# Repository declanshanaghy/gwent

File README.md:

# Gwent Companion

<div align="center">
  
</div>

A Raspberry Pi-based digital companion for the physical card game Gwent from The Witcher III. Players use RFID-tagged physical cards; the companion tracks scores, manages game state, and guides players through the game.

```mermaid
%%{init: {
  'theme': 'base',
  'themeVariables': {
    'primaryColor': '#6d1a36',
    'primaryTextColor': '#333',
    'primaryBorderColor': '#7C4DFF',
    'lineColor': '#7C4DFF',
    'secondaryColor': '#D7CCC8',
    'tertiaryColor': '#EFEBE9',
    'fontFamily': 'Courier New',
    'fontSize': '16px'
  }
}}%%

flowchart LR
    subgraph physical["🃏 Physical Layer"]
        cards["💳 RFID Cards"]
        mat["🧵 Game Mat"]
    end

    subgraph hw["🔧 Hardware"]
        rfid["📡 RFID Reader"]
        matrix["🔢 LED Matrices"]
        touch["🖐️ 7\" Touchscreen"]
        camhw["📷 NoIR Camera"]
    end

    subgraph server["💻 Game Server"]
        gwent["🎮 gwent service"]
        mqtt_pub["📨 MQTT Publisher"]
    end

    camsvc["📷 gwent-camera\n+ nginx :80"]
    broker["📡 MQTT Broker\nMosquitto"]

    subgraph clients["👁️ Kiosk & Drivers"]
        tui["📊 gwent-tui\n(touchscreen kiosk)"]
        loop["🤖 game-loop.py"]
    end

    cards -.- rfid
    rfid --- gwent
    matrix --- gwent
    gwent --- mqtt_pub
    mqtt_pub --> broker
    broker <--> tui
    broker <--> loop
    tui --- touch
    camsvc --> camhw
    tui -.->|"/camera/*"| camsvc

    classDef hardware fill:#A1887F,stroke:#5D4037,stroke-width:2px,color:#fff,font-family:'Courier New',font-weight:bold
    classDef software fill:#BCAAA4,stroke:#5D4037,stroke-width:2px,color:#3E2723,font-family:'Courier New',font-weight:bold
    classDef data fill:#D7CCC8,stroke:#5D4037,stroke-width:2px,color:#3E2723,font-family:'Courier New',font-style:italic

    class cards,mat data
    class rfid,matrix,touch,camhw hardware
    class gwent,mqtt_pub,broker,tui,loop,camsvc software
```

## How It Works

1. The `gwent` system service runs on a Raspberry Pi, managing game state and driving all hardware. It always has a game in progress — a fresh random game is dealt at startup and after every Game Over
2. Players scan RFID-tagged cards on the reader to play cards; the 7" touchscreen runs the `gwent-tui` kiosk for assignment, menus, and live view
3. The server publishes every game state change over MQTT, including a retained full-state snapshot on `gwent/server/state`
4. Clients consume that retained snapshot — there is no HTTP API on the game server; all command and control is over MQTT (`gwent/ctrl/*` in)
5. The **gwent-tui** terminal dashboard subscribes to MQTT and renders a live view of the game on the touchscreen
6. The **game-loop.py** orchestrator pits two LLM models against each other by reading the retained snapshot and publishing moves over MQTT
7. A separate **gwent-camera** service drives a Pi NoIR camera and serves stills, an MJPEG stream, and game recordings over HTTP (nginx `/camera/*`)

## Components

### Game Server (`software/gwent/`)

The core Python service. Runs as a systemd unit (`gwent`).

- **Game stages state machine** -- DealCards, PlayRound, RoundEnd, GameOver (auto-dealt; there is no main menu)
- **MQTT command & control** -- all events and full game state are published to `gwent/` topics via a Mosquitto broker. State is a retained snapshot on `gwent/server/state`; commands (players, client-tts) come in on `gwent/ctrl/*`. No HTTP.
- **Hardware abstraction layer** -- SPI (RFID RC522), I2C (TCA9548A mux, IS31FL3731 LED matrices). The legacy SSD1306 OLED + rotary-encoder MFD drivers remain in the tree but are disabled (`GWENT_DISABLE_MFD=true`) and physically removed
- **Audio system** -- sound effects and TTS announcements (multiple providers: gTTS, ElevenLabs, OpenAI, Piper, macOS `say`)

### Terminal Dashboard (`software/gwent-tui/`)

A [Textual](https://textual.textualize.io/)-based Rich terminal app that renders a live game dashboard, running as the touchscreen kiosk (greetd → cage → kitty → gwent-tui, with a `gwent-touch` evdev bridge). Subscribes to MQTT — including the retained `gwent/server/state` snapshot — and provides hamburger-menu controls (player assignment, camera on/off, live view) plus a floating camera live-view panel. Stage-specific widgets mirror the server's state machine.

### LLM-vs-LLM Orchestrator (`.claude/skills/llm-vs/scripts/game-loop.py`)

Drives fully automated games between two LLM models. Supports multiple providers (Anthropic, OpenAI, Google Gemini, Ollama) with model aliases. Reads game state from the retained `gwent/server/state` MQTT snapshot, constructs prompts with full board context, and submits moves via MQTT.

### Camera Service (`scripts/camera-server.py`)

A standalone `gwent-camera` systemd service (system Python + picamera2) owns the Pi NoIR camera and exposes stills, an MJPEG stream, and game recordings via nginx on port 80 (`/camera/{still,stream,recordings/}`). It is also an MQTT client (`gwent/camera/ctrl` in, retained `gwent/camera/state` out) and records each game to H.264 with a 10 GiB disk budget.

### Shared Utilities (`software/gwent-shared/`)

TTS provider abstractions shared between server and TUI. No hardware dependencies.

## Hardware

| Bus | Device | Purpose |
|-----|--------|---------|
| SPI CE0 | MFRC522 | RFID card reader |
| I2C (via TCA9548A mux) | IS31FL3731 Ch 0 | Gem display (lives) |
| I2C (via TCA9548A mux) | IS31FL3731 Ch 1 | Player 1 score |
| I2C (via TCA9548A mux) | IS31FL3731 Ch 2 | Player 2 score |
| DSI / USB | 7" Touchscreen | Kiosk UI (gwent-tui) + speakers |
| CSI | Pi NoIR Camera (IMX219) | Table view, stills/stream, game recordings |

## Card Data

Each card is a JSON file in `software/data/cards/{Faction}/CardName.json`:

```json
{
  "faction": "Monsters",
  "name": "Arachas: 1",
  "strength": 4,
  "ranges": ["close"],
  "abilities": ["muster"],
  "starter": true,
  "rfid": 622264733154
}
```

Five factions: **Monsters**, **Nilfgaardian**, **Northern Realms**, **Scoiatael**, **Skellige**, plus **Neutral** cards.

## Development

```bash
# Start the dev server
bash scripts/dev-server.sh gwent start

# Dump current game state (retained snapshot)
mosquitto_sub -h localhost -u geralt -P gwent -t gwent/server/state -C 1

# Run the TUI
gwent-tui

# Run an LLM vs LLM game
python3 .claude/skills/llm-vs/scripts/game-loop.py \
  --model-p1 anthropic/sonnet --model-p2 gemini/flash
```

Always use `SIGTERM` for graceful shutdown (never `SIGKILL`) -- hardware cleanup is required.

## Documentation

| Document | Description |
|----------|-------------|
| [Architecture](design/GwentArchitecture.md) | Full system architecture reference |
| [Game Rules](design/GwentRules.md) | Canonical Gwent rules as implemented |
| [Game Stages](design/GwentGameStages.md) | State machine and flow diagrams |
| [PubSub Architecture](design/GwentPubSub.md) | MQTT messaging system design |
| [Product Requirements](design/000-product-requirements.md) | Original PRD |
| [Mermaid Style Guide](design/MermaidStyleGuide.md) | Diagram styling conventions |

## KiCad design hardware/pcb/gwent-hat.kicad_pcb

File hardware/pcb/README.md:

# Gwent HAT — KiCad project

A Raspberry Pi 4 HAT carrier PCB for the Gwent Companion. Hosts headers and Qwiic connectors so the existing breakout modules (MFRC522, SSD1306 OLED, TCA9548A mux, three IS31FL3731 charlieplex matrices, PEC11 rotary encoder) plug in without re-soldering. Targets fabrication at JLCPCB.

> Canonical hardware spec: [`design/tasks/011-hardware-specification.md`](../../design/tasks/011-hardware-specification.md). If anything in the schematic conflicts with that doc, the doc wins — fix the schematic.

## Quick facts

| | |
|---|---|
| Form factor | Raspberry Pi HAT (65 × 56.5 mm) |
| Layers | 2 |
| Substrate | FR4, 1.6 mm, 1 oz copper, ENIG (or HASL for cheap) |
| Connectors | 2×20 GPIO stacking header, 1×8 RC522 header, 1×16 OLED header, 4× Qwiic JST-SH (mux + 3 matrices), PEC11 footprint |
| Library deps | KiCad 9 built-in libraries only (Connector, Connector_Generic, Connector_JST, Switch). SparkFun KiCad library optional for prettier Qwiic 3D models. |
| Power | 5V / 3.3V tapped from Pi GPIO header (no on-board regulator) |
| Target fab | JLCPCB, 5 boards (~$5 unassembled, ~$25 with header assembly) |

## Required tools

- **KiCad 9.x** — https://www.kicad.org/download/
- **git** with submodule support
- (optional) **JLCPCB plugin for KiCad** — https://github.com/Bouni/kicad-jlcpcb-tools — generates BOM and pick-and-place files in the format JLCPCB wants

Once KiCad is installed, open `gwent-hat.kicad_pro` and KiCad will pull in the project's symbol/footprint library tables (in `sym-lib-table` / `fp-lib-table`) which point at the vendored libs in `libs/`.

## First-time setup

```bash
cd hardware/pcb
open gwent-hat.kicad_pro          # macOS
# or
xdg-open gwent-hat.kicad_pro      # Linux
```

KiCad will create the schematic (`gwent-hat.kicad_sch`) and PCB (`gwent-hat.kicad_pcb`) on first save if they don't already exist. All symbols and footprints come from KiCad's bundled libraries — no extra setup required.

### Optional: SparkFun KiCad library (for nicer Qwiic visuals)

```bash
# From hardware/pcb/
git clone --depth 1 https://github.com/sparkfun/SparkFun-KiCad-Libraries.git libs/sparkfun-kicad
# Then in KiCad: Preferences → Manage Symbol Libraries → add libs/sparkfun-kicad
#                Preferences → Manage Footprint Libraries → add libs/sparkfun-kicad/footprints
```

This isn't required — KiCad's `Connector_JST:JST_SH_*` symbols are functionally equivalent — but the SparkFun version comes with proper Qwiic-branded silkscreen and 3D models.

## How the project is organized

| File | What it is |
|---|---|
| `gwent-hat.kicad_pro` | KiCad project metadata |
| `gwent-hat.kicad_sch` | Schematic |
| `gwent-hat.kicad_pcb` | PCB layout (board outline pre-drawn to Pi HAT spec) |
| `sym-lib-table` | Project-scoped symbol library list |
| `fp-lib-table` | Project-scoped footprint library list |
| `BUILD.md` | Step-by-step schematic placement guide |
| `BOM.md` | Bill of materials with manufacturer part numbers and JLCPCB/LCSC sourcing |
| `libs/` | (Optional) Vendored EDA libraries — only needed for SparkFun Qwiic visuals |
| `fab/` | Fabrication outputs (Gerbers, drill, BOM, CPL) — only versioned zips are committed |
| `docs/netlist.md` | Canonical net-by-net pin assignments — the source of truth for the schematic |

## Workflow

1. **Schematic** — open `gwent-hat.kicad_sch` and follow [`BUILD.md`](BUILD.md) step by step. Place every symbol from the BOM, wire nets per [`docs/netlist.md`](docs/netlist.md), assign footprints, run ERC.
2. **PCB layout** — Tools → Update PCB from Schematic. Footprints will appear inside the pre-drawn board outline. Place, route, run DRC. Match design rules to JLCPCB's "2-layer, 6/6 mil min trace, 0.3 mm min hole" capability tier.
3. **Fab outputs** — File → Plot → Gerbers (use the JLCPCB-friendly settings documented in `BUILD.md`), then File → Fabrication Outputs → Drill Files. Run the JLCPCB plugin to generate BOM + CPL CSVs.
4. **Order** — zip the Gerber/drill/BOM/CPL set into `fab/gwent-hat-v1.0-jlcpcb.zip`, upload to https://jlcpcb.com, pick stackup + finish + quantity, pay.

## Versioning

- `v1.0` — initial Pi HAT carrier with breakouts on headers/Qwiic
- `v1.1` — corrections from first fab run (TBD)
- `v2.0` — integrate IS31FL3731 + LEDs and TCA9548A onto the board (TBD)

Each fab order zip is committed under `fab/gwent-hat-vN.M-jlcpcb.zip` so the as-fabbed artifact is always reproducible.

## Status

- [x] Project scaffold (this commit)
- [x] Canonical netlist documented (`docs/netlist.md`)
- [x] Bill of materials (`BOM.md`)
- [x] Build guide (`BUILD.md`)
- [x] Project file (`gwent-hat.kicad_pro`)
- [x] Schematic with all symbols placed (`gwent-hat.kicad_sch`, generated by `scripts/gen_schematic.py`)
- [ ] Schematic wired (add wires + net labels per `BUILD.md`)
- [ ] ERC clean
- [ ] Board outline drawn to Pi HAT spec on `Edge.Cuts` layer
- [ ] PCB placement
- [ ] PCB routing
- [ ] DRC clean
- [ ] Gerbers exported
- [ ] BOM + CPL generated
- [ ] First boards ordered

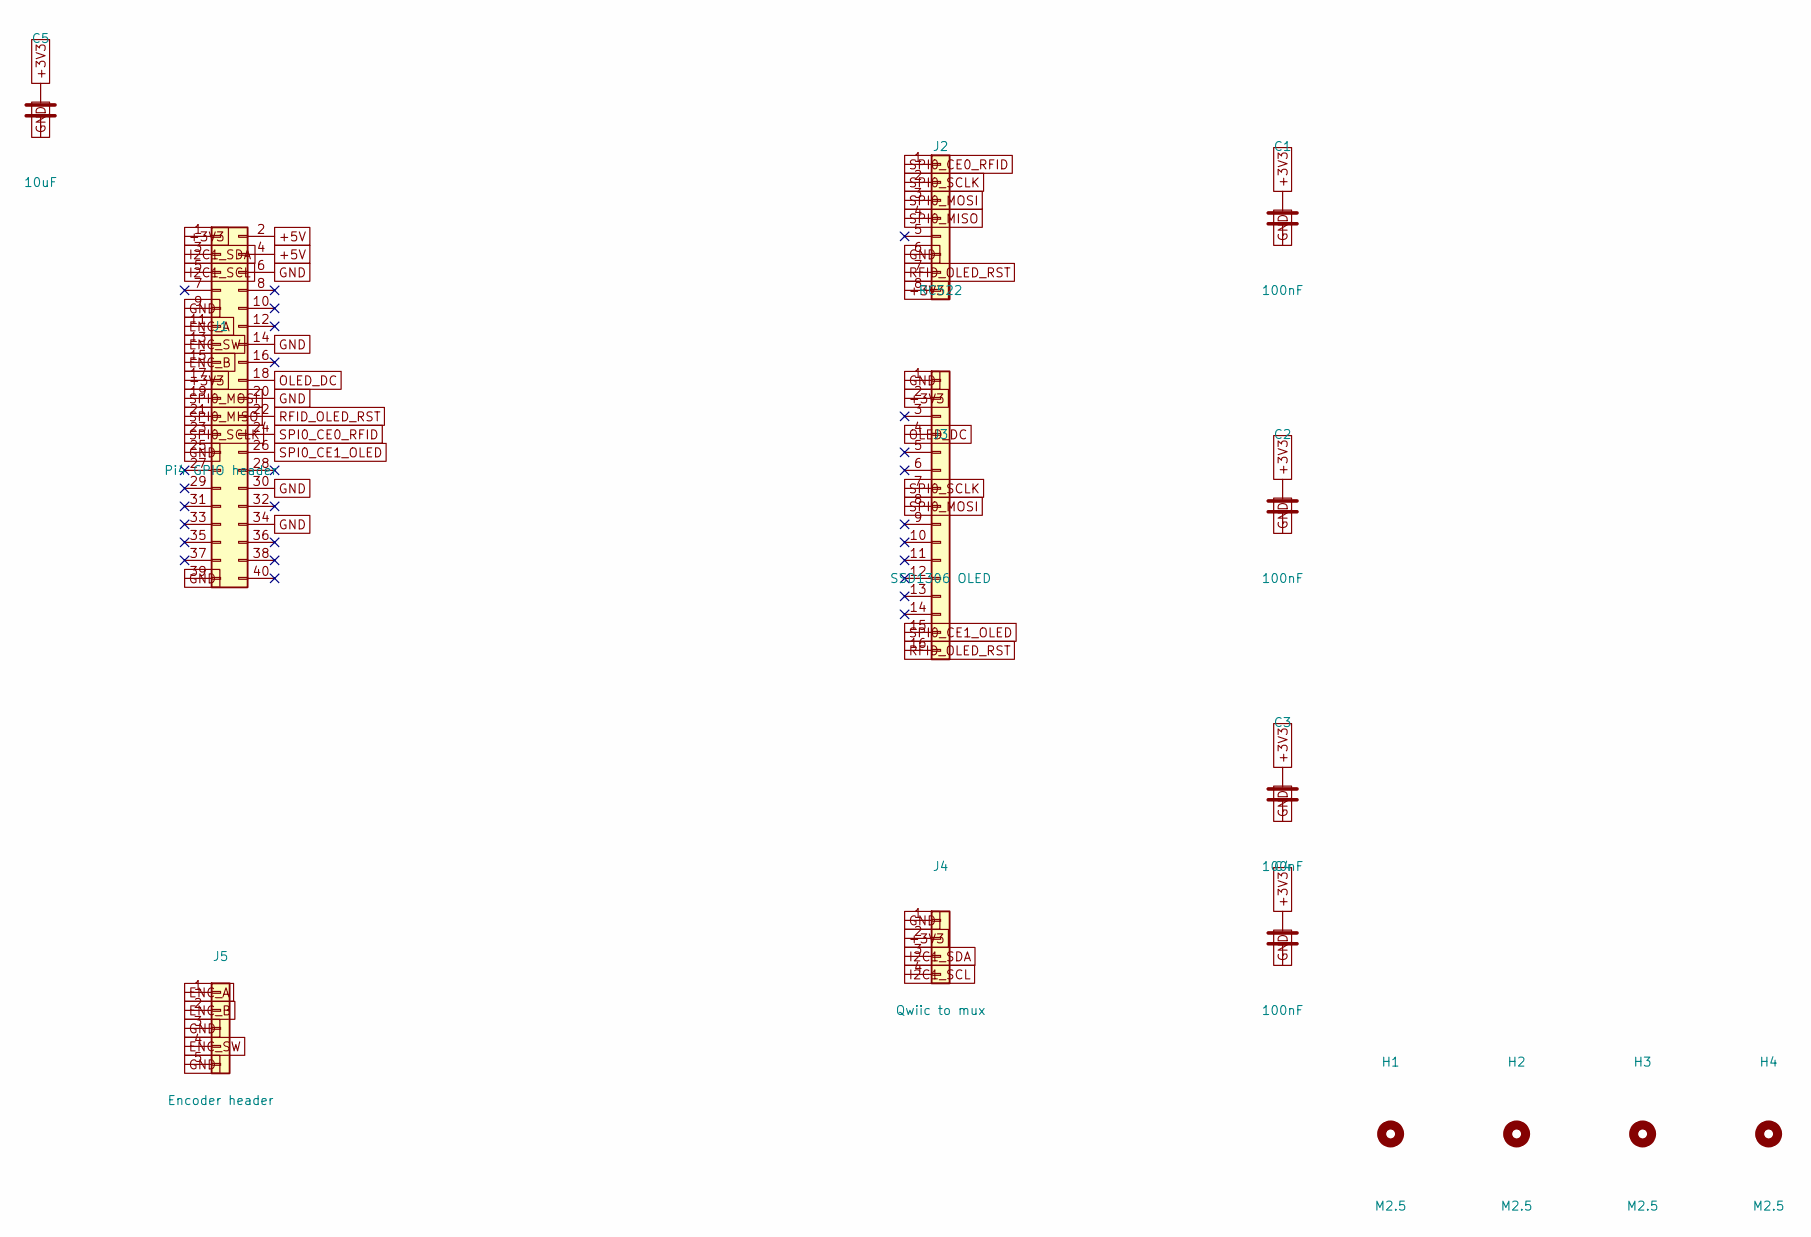
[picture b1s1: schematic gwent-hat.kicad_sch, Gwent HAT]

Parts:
C1, C2, C3, C4: 100nF; C_0805_2012Metric
C5: 10uF; C_0805_2012Metric
H1, H2, H3, H4: M2.5; MountingHole_2.7mm_M2.5_DIN965_Pad
J1: Pi4 GPIO header; PinHeader_2x20_P2.54mm_Vertical
J2: RC522; PinHeader_1x08_P2.54mm_Vertical
J3: SSD1306 OLED; PinHeader_1x16_P2.54mm_Vertical
J4: Qwiic to mux; JST_SH_SM04B-SRSS-TB_1x04-1MP_P1.00mm_Horizontal
J5: Encoder header; PinHeader_1x05_P2.54mm_Vertical

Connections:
+3V3: C1.1, C2.1, C3.1, C4.1, C5.1, J1.1, J1.17, J2.8, J3.2, J4.2
+5V: J1.2, J1.4
ENC_A: J1.11, J5.1; also elsewhere on the board
ENC_B: J1.15, J5.2; also elsewhere on the board
ENC_SW: J1.13, J5.4; also elsewhere on the board
GND: C1.2, C2.2, C3.2, C4.2, C5.2, J1.6, J1.9, J1.14, J1.20, J1.25, J1.30, J1.34, J1.39, J2.6, J3.1, J4.1, J5.3, J5.5; also elsewhere on the board
I2C1_SCL: J1.5, J4.4
I2C1_SDA: J1.3, J4.3
OLED_DC: J1.18, J3.4
RFID_OLED_RST: J1.22, J2.7, J3.16
SPI0_CE0_RFID: J1.24, J2.1
SPI0_CE1_OLED: J1.26, J3.15
SPI0_MISO: J1.21, J2.4
SPI0_MOSI: J1.19, J2.3, J3.8
SPI0_SCLK: J1.23, J2.2, J3.7

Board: 2 copper layers, 14 parts (0 on the bottom side), 15 nets, no tracks yet.

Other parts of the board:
SW1: PEC11; RotaryEncoder_Alps_EC11E-Switch_Vertical_H20mm

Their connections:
ENC_A: SW1.A; also elsewhere on the board
ENC_B: SW1.B; also elsewhere on the board
ENC_SW: SW1.S1; also elsewhere on the board
GND: SW1.C, SW1.S2; also elsewhere on the board

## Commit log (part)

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2020-06-16 Adding logging
2020-06-18 Adding new deps
2020-11-23 reactiving project
2020-11-25 OLED Display integrated
2025-04-20 Add task-master AI and Roo Code framework for Gwent game development without asyncio
2025-04-20 Remove submodule directories and cleanup unused code
2025-04-20 Rename mock_demo.py to demo_mock.py and add mock demo functionality
2025-04-20 Update system configuration and communication modules
    - Modified system configuration files (gwent.service, install-vars.sh, setup_raspberry_pi.sh)
    - Updated MQTT and Redis communication modules
    - Updated package setup files
    - Removed .env.example file
    - Updated development workflow documentation
2025-04-20 docs: Add Raspberry Pi validation rule to dev workflow
2025-04-20 Migrating from asyncio to simple shit with Task Master & RooCode (#2)
    # Task Master Integration and Project Restructuring
    This PR introduces the Task Master system for AI-driven development and significantly restructures the Gwent project for improved modularity, testability, and hardware abstraction.
    ## 🧠 Task Master Integration
    * **dc5b325** Add task-master AI and Roo Code framework for Gwent game development without asyncio
    * **47e636f** docs: update ADR with Task Master implementation details
    * **7c9b59a** Reorganize design documentation structure and update dev workflow
2025-04-21 fix: Update luma.examples submodule path in .gitmodules
2025-04-21 fix: Add MANIFEST.in to include JSON schema files and fix MFRC522 compatibility
2025-04-21 fix: Use noop GPIO and handle None device in SSD1325Presenter
2025-04-21 Change SPI port from 0 to 1 for SSD1325Presenter
2025-04-21 Replace gaugette rotary encoder with direct RPi.GPIO implementation
2025-04-21 Separate DirectGPIORotaryEncoder into its own module
2025-04-21 Add test_rotary_gpio.py to match renamed module
2025-04-21 Update rotary_gpio.py to handle sysfs permission issues with a fallback implementation
2025-04-23 Refactor deployment and service management scripts
    - Consolidate deployment scripts into Makefile targets
    - Update install-system.sh with improved dependency management and WiringPi installation
    - Convert update-service.sh from remote to local operations
    - Add better error handling and service status checks
    - Update Makefile paths and add update-service target
    - Improve service management with auto-detection and boot enabling
2025-04-23 Remove original rotary_simple.py file after renaming to rotary_rawgpio.py
2025-04-24 Refactor hardware interface with RPi.GPIO implementation
    - Add new rotary encoder implementation using RPi.GPIO
    * Add DirectGPIORotaryEncoder and DirectGPIOSwitch classes
    * Update rotary_chooser to use RPi.GPIO implementation as default
    * Remove deprecated rotary_rawgpio implementation
    - Add RFID functionality
    * Add MFRC522-python as git submodule
2025-04-24 Enhance MQTT configuration and remove Redis dependencies
    - main.py: Rename close_redis() to close_pubsub() for clarity, add MQTT authentication
    - install-system.sh: Add Mosquitto configuration with password auth, reorganize dependencies
    - gwent.service: Remove Redis service dependencies, keep only Mosquitto
    - Makefile: Update game target to use rsync instead of install-system
    - test_displays.py: Add comprehensive documentation, error handling, and improve display testing
    - Remove unused Redis proof-of-concept script (redispoc.py)
2025-04-24 Add node_modules to .gitignore
2025-04-24 Fix display issues and add diagnostic tools
    - Enhanced SSD1306 presenter with maximum contrast and reset sequence
    - Added display refresh logic to ensure content is visible
    - Created diagnostic tools for troubleshooting display issues
    - Applied consistent naming convention to files
    - Updated build system with new targets
2025-04-24 Refactor: Convert asyncio architecture to threading-based architecture
    This commit refactors the entire application architecture from asyncio to threading:
    1. Core Architecture Changes:
    - Replaced asyncio with threading for better compatibility and performance
    - Implemented thread-safe communication between components using MQTT
    - Created ThreadComponent base class for consistent component lifecycle management
    - Added proper thread management with start/stop/shutdown methods
2025-04-25 Restore and update PDF documentation
    - Restored GwentPubSub.pdf and GwentGameStages.pdf from git hash 09c3e900218edf34832cb47ec9adaa71139782e6
    - Renamed 'Gwent PubSub.pdf' to 'GwentPubSub.pdf' to remove space
    - Updated design/README.md with references to PDF documentation
    - Updated main README.md to reference design documentation and PDF files
    - Added PDF documentation section with descriptions of each file
2025-04-25 Add l33tC0dzr architecture diagram style requirements
    - Added style rule to dev_workflow.mdc requiring architecture diagrams to use the 'latte drinking l33tC0dzr' style
    - Updated DesignDocumentationStyleGuide.md to match the new style requirements
    - Restored hipster style to GwentPubSub.md as a reference implementation
    - Added emoji and creative naming throughout the documentation
    - Kept the mood light while maintaining readability
2025-04-25 Update GPIO pin connections in SETUP_INSTRUCTIONS.md
    - Updated GPIO pin connections table based on actual code in software/gwent/gwent/hal
    - Added mermaid diagram showing Raspberry Pi GPIO pinout with used pins highlighted
    - Added reference to external Raspberry Pi pinout image
    - Fixed incorrect pin assignments for rotary encoder
    - Clarified shared pins between components
2025-04-25 Comprehensive documentation improvements
    - Updated SETUP_INSTRUCTIONS.md with manual setup steps from scripts/install-system.sh
    - Added link to SETUP_INSTRUCTIONS.md from software/gwent/gwent/poc/README.md
    - Created new scripts/README.md with descriptions of all scripts and link to README-task-master.md
    - Enhanced README.md with additional emojis and image placeholders to follow documentation style guide
    - Fixed section numbering in SETUP_INSTRUCTIONS.md
2025-04-25 Fix mermaid diagrams and add SVG logo
    - Fixed Overview flowchart by renaming 'end' class to 'endNode' to avoid reserved keyword
    - Fixed Project Status gantt chart with proper date format and explicit end dates
    - Created SVG logo in 16:9 format with 'Cards & Circuits' tagline
    - Integrated SVG logo into README.md
    - Removed mermaid logo diagram in favor of SVG logo
2025-04-25 fix(rotary): Add PiGPIO implementation for rotary encoder
    This commit adds a new implementation for the rotary encoder using the pigpio library,
    which resolves issues with rotation detection when other GPIO services are running.
    - Added PiGPIORotaryEncoder and PiGPIOSwitch classes
    - Updated rotary_chooser.py to include the new implementation
    - Made PiGPIO the default implementation in rotary.py
    - Added diagnostic tools for GPIO service management
2025-04-25 Update MFD diagnostic tool to wait for user feedback between tests
2025-04-25 Fix POC targets and improve system setup
    This commit includes several improvements to the Gwent project:
    1. Fixed discrepancies between Makefile POC targets and setup.py entry points:
    - Added missing entry points for mfd-diagnostic, rotary-diagnostics, rotary-robust, rotary-lgpio, and rotary-test
    - Fixed naming discrepancies by changing rotary-diagnostic-test to rotary-diagnostic
    - Added separate entry points for gpio-service-stop and gpio-service-start
    - Verified correct module path mappings for matrix-test, oled-direct-test, and display-diagnostic
2025-04-26 Add pr_description.md to .gitignore
2025-04-26 Enhanced OLED menu design with improved visual aesthetics
    This commit includes the following changes:
    1. Created a visually appealing HTML menu designer for the OLED display
    2. Implemented 10 different theme options with l33tc0dzr style naming
    3. Added a recommended theme (Th3Ch0zen1) with special highlighting
    4. Each theme includes mockups for menus, prompts, and error displays
    5. Enhanced the Th3Ch0zen1 theme with:
2025-04-26 OLED Menu Design Enhancement (#8)
    OLED Menu Design Enhancement
    This PR introduces a visually appealing HTML menu designer for the OLED display used in the Gwent project. The design provides multiple theme options with a focus on readability and aesthetics while 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
    Summary of Changes
    17 files changed with 2260 insertions(+) and 248 deletions(-)
    Created a visually appealing HTML menu designer for the OLED display (658 lines)
    Implemented 10 different theme options with l33tc0dzr style naming
2025-04-26 Menu Beautification 2: Enhanced OLED Display & Card Utilities Refactoring (#9)
    * Enhanced OLED menu design with improved visual aesthetics
    This commit includes the following changes:
    1. Created a visually appealing HTML menu designer for the OLED display
    2. Implemented 10 different theme options with l33tc0dzr style naming
    3. Added a recommended theme (Th3Ch0zen1) with special highlighting
    4. Each theme includes mockups for menus, prompts, and error displays
2025-04-27 Add card downloader utility for Skellige Gwent deck
    Added a new utility to download and compare Skellige Gwent cards from the Witcher Wiki.
    Key features:
    - Downloads HTML content from the Witcher Wiki
    - Parses card information from tables, lists, and paragraphs
    - Compares with existing card files
    - Generates a detailed comparison report
2025-04-28 Improved error handling with stack traces and converted RFID reader to local variables
    Key improvements:
    1. Converted RFID Reader to Local Variables:
    - Changed self._rfid_reader from a class member to local variables
    - Updated all methods to create their own instances when needed
    - Removed unnecessary cleanup code
    2. Added Stack Traces to All Exception Handlers:
2025-04-28 updated dev rules
2025-04-28 Updated MFRC522 lib
2025-04-28 Add comprehensive Gwent card database analysis report
    This commit adds a detailed Markdown report analyzing the Gwent card database with the following sections:
    - Card Distribution by Faction
    - Card Ownership Summary
    - Card Statistics (overall stats, card types, leader cards, abilities, RFID, hero cards, weather cards)
    - Cards by Faction (leaders and regular cards)
    - Anomalies analysis
2025-04-29 Updated lib
2025-04-29 Implement player score display and fix deck registration
    Key Changes:
    1. Fixed RegisterDecks class to properly collect cards and pass them to complete() callback
    - Added player tracking and deck collection logic
    - Fixed the bug where complete() was called without required deck1 and deck2 parameters
    - Improved user feedback during deck registration process
    2. Implemented player score display functionality
2025-04-30 tweak logging in MFRC522-pytho
2025-04-30 Separate PubSub functionality from ThreadComponent
2025-04-30 Revert "last remaining issue is MFD thread join on shutdown"
    This reverts commit c48f5adb711ab1cf7a8c7bea0e909a28128070cc.
2025-06-24 Bump pbkdf2 from 3.0.17 to 3.1.3 in /software/glory-gate
    Bumps [pbkdf2](https://github.com/crypto-browserify/pbkdf2) from 3.0.17 to 3.1.3.
    - [Changelog](https://github.com/browserify/pbkdf2/blob/master/CHANGELOG.md)
    - [Commits](https://github.com/crypto-browserify/pbkdf2/compare/v3.0.17...v3.1.3)
    ---
    updated-dependencies:
    - dependency-name: pbkdf2
2025-11-18 Bump js-yaml from 3.13.1 to 3.14.2 in /software/glory-gate
    Bumps [js-yaml](https://github.com/nodeca/js-yaml) from 3.13.1 to 3.14.2.
    - [Changelog](https://github.com/nodeca/js-yaml/blob/master/CHANGELOG.md)
    - [Commits](https://github.com/nodeca/js-yaml/compare/3.13.1...3.14.2)
    ---
    updated-dependencies:
    - dependency-name: js-yaml
2026-03-25 adding mermaid design
